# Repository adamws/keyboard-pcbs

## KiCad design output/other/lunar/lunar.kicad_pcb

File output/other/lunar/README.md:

## other/lunar

[layout](lunar-kle.json) - [PCB](lunar.kicad_pcb)

{:loading="lazy"}

[Open in keyboard-layout-editor](http://www.keyboard-layout-editor.com/##@@=0,0&=0,1&=0,2&=0,3&=0,4&=0,5&=0,6&=0,7&=0,8&=0,9&=0,10&=0,11&=0,12&=0,13&=2,12&=0,14;&@_w:1.5;&=1,0&=1,1&=1,2&=1,3&=1,4&=1,5&=1,6&=1,7&=1,8&=1,9&=1,10&=1,11&=1,12&_w:1.5;&=1,13&=1,14;&@_w:1.75;&=2,0&=2,1&=2,2&=2,3&=2,4&=2,5&=2,6&=2,7&=2,8&=2,9&=2,10&=2,11&_w:2.25;&=2,13&=2,14;&@_w:2.25;&=3,0&=3,1&=3,2&=3,3&=3,4&=3,5&=3,6&=3,7&=3,8&=3,9&=3,10&_w:1.75;&=3,11&=3,13&=3,14;&@_w:1.5;&=4,0&_w:1.25;&=4,1&_w:1.5;&=4,2&_w:2.25;&=4,3&_w:1.5;&=4,5&_w:2.75;&=4,7&_w:1.25;&=4,9&=4,10&=4,11&=4,13&=4,14)

{:loading="lazy"}

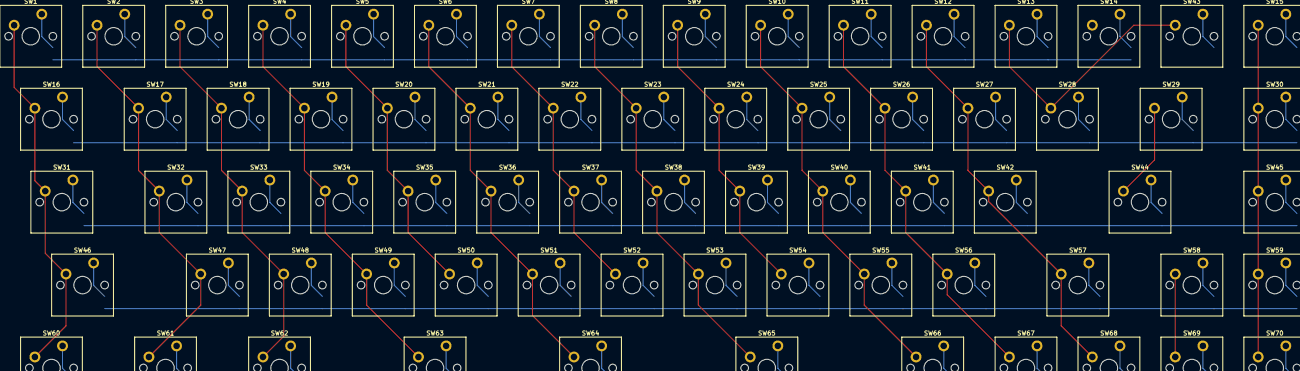
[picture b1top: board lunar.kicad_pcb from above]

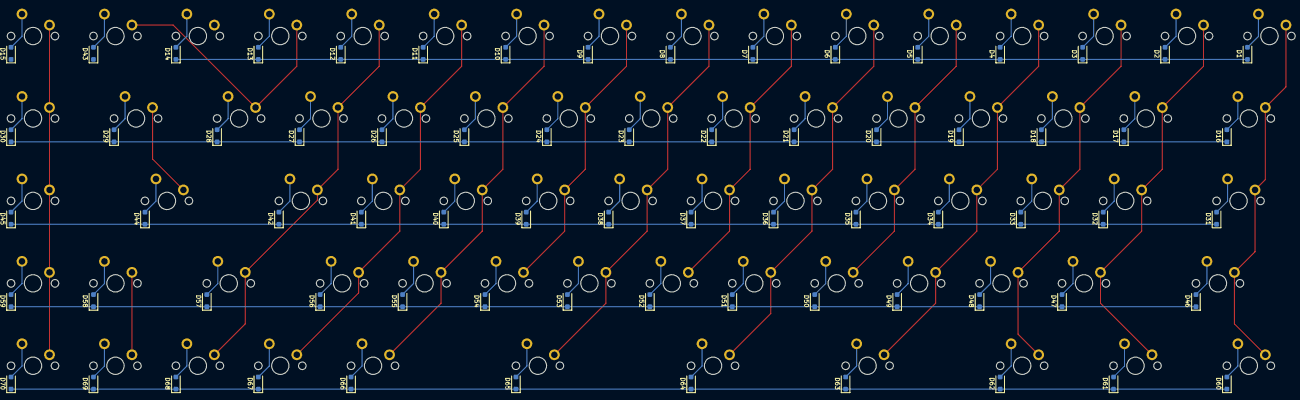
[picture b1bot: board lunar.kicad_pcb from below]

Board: 2 copper layers, 140 parts (70 on the bottom side), 90 nets.

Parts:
D1, D2, D3, D4, D5, D6, D7, D8, D9, D10, D11, D12, D13, D14, D15, D16, D17, D18, D19, D20, D21, D22, D23, D24, D25, D26, D27, D28, D29, D30, D31, D32, D33, D34, D35, D36, D37, D38, D39, D40, D41, D42, D43, D44, D45, D46, D47, D48, D49, D50, D51, D52, D53, D54, D55, D56, D57, D58, D59, D60, D61, D62, D63, D64, D65, D66, D67, D68, D69, D70: D_SOD-123F
SW1, SW2, SW3, SW4, SW5, SW6, SW7, SW8, SW9, SW10, SW11, SW12, SW13, SW14, SW15, SW16, SW17, SW18, SW19, SW20, SW21, SW22, SW23, SW24, SW25, SW26, SW27, SW28, SW29, SW30, SW31, SW32, SW33, SW34, SW35, SW36, SW37, SW38, SW39, SW40, SW41, SW42, SW43, SW44, SW45, SW46, SW47, SW48, SW49, SW50, SW51, SW52, SW53, SW54, SW55, SW56, SW57, SW58, SW59, SW60, SW61, SW62, SW63, SW64, SW65, SW66, SW67, SW68, SW69, SW70: SW_Cherry_MX_PCB_1.00u

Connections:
COL0: SW1.1, SW16.1, SW31.1, SW46.1, SW60.1
COL1: SW2.1, SW17.1, SW32.1, SW47.1, SW61.1
COL2: SW3.1, SW18.1, SW33.1, SW48.1, SW62.1
COL3: SW4.1, SW19.1, SW34.1, SW49.1, SW63.1
COL4: SW5.1, SW20.1, SW35.1, SW50.1
COL5: SW6.1, SW21.1, SW36.1, SW51.1, SW64.1
COL6: SW7.1, SW22.1, SW37.1, SW52.1
COL7: SW8.1, SW23.1, SW38.1, SW53.1, SW65.1
COL8: SW9.1, SW24.1, SW39.1, SW54.1
COL9: SW10.1, SW25.1, SW40.1, SW55.1, SW66.1
COL10: SW11.1, SW26.1, SW41.1, SW56.1, SW67.1
COL11: SW12.1, SW27.1, SW42.1, SW57.1, SW68.1
COL12: SW13.1, SW28.1, SW43.1
COL13: SW14.1, SW29.1, SW44.1, SW58.1, SW69.1
COL14: SW15.1, SW30.1, SW45.1, SW59.1, SW70.1
unnamed: D1.2, SW1.2
unnamed: D2.2, SW2.2
unnamed: D3.2, SW3.2
unnamed: D4.2, SW4.2
unnamed: D5.2, SW5.2
unnamed: D6.2, SW6.2
unnamed: D7.2, SW7.2
unnamed: D8.2, SW8.2
unnamed: D9.2, SW9.2
unnamed: D10.2, SW10.2
unnamed: D11.2, SW11.2
unnamed: D12.2, SW12.2
unnamed: D13.2, SW13.2
unnamed: D14.2, SW14.2
unnamed: D15.2, SW15.2
unnamed: D16.2, SW16.2
unnamed: D17.2, SW17.2
unnamed: D18.2, SW18.2
unnamed: D19.2, SW19.2
unnamed: D20.2, SW20.2
unnamed: D21.2, SW21.2
unnamed: D22.2, SW22.2
unnamed: D23.2, SW23.2
unnamed: D24.2, SW24.2
unnamed: D25.2, SW25.2
unnamed: D26.2, SW26.2
unnamed: D27.2, SW27.2
unnamed: D28.2, SW28.2
unnamed: D29.2, SW29.2
unnamed: D30.2, SW30.2
unnamed: D31.2, SW31.2
unnamed: D32.2, SW32.2
unnamed: D33.2, SW33.2
unnamed: D34.2, SW34.2
unnamed: D35.2, SW35.2
unnamed: D36.2, SW36.2
unnamed: D37.2, SW37.2
unnamed: D38.2, SW38.2
unnamed: D39.2, SW39.2
unnamed: D40.2, SW40.2
unnamed: D41.2, SW41.2
unnamed: D42.2, SW42.2
unnamed: D43.2, SW43.2
unnamed: D44.2, SW44.2
unnamed: D45.2, SW45.2
unnamed: D46.2, SW46.2
unnamed: D47.2, SW47.2
unnamed: D48.2, SW48.2
unnamed: D49.2, SW49.2
unnamed: D50.2, SW50.2
unnamed: D51.2, SW51.2
unnamed: D52.2, SW52.2
unnamed: D53.2, SW53.2
unnamed: D54.2, SW54.2
unnamed: D55.2, SW55.2
unnamed: D56.2, SW56.2
unnamed: D57.2, SW57.2
unnamed: D58.2, SW58.2
unnamed: D59.2, SW59.2
unnamed: D60.2, SW60.2
unnamed: D61.2, SW61.2
unnamed: D62.2, SW62.2
unnamed: D63.2, SW63.2
unnamed: D64.2, SW64.2
unnamed: D65.2, SW65.2
unnamed: D66.2, SW66.2
unnamed: D67.2, SW67.2
unnamed: D68.2, SW68.2
unnamed: D69.2, SW69.2
unnamed: D70.2, SW70.2
ROW0: D1.1, D2.1, D3.1, D4.1, D5.1, D6.1, D7.1, D8.1, D9.1, D10.1, D11.1, D12.1, D13.1, D14.1, D15.1
ROW1: D16.1, D17.1, D18.1, D19.1, D20.1, D21.1, D22.1, D23.1, D24.1, D25.1, D26.1, D27.1, D28.1, D29.1, D30.1
ROW2: D31.1, D32.1, D33.1, D34.1, D35.1, D36.1, D37.1, D38.1, D39.1, D40.1, D41.1, D42.1, D43.1, D44.1, D45.1
ROW3: D46.1, D47.1, D48.1, D49.1, D50.1, D51.1, D52.1, D53.1, D54.1, D55.1, D56.1, D57.1, D58.1, D59.1
ROW4: D60.1, D61.1, D62.1, D63.1, D64.1, D65.1, D66.1, D67.1, D68.1, D69.1, D70.1

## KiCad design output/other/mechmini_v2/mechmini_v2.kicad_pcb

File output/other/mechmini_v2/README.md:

## other/mechmini_v2

[layout](mechmini_v2-kle.json) - [PCB](mechmini_v2.kicad_pcb)

{:loading="lazy"}

[Open in keyboard-layout-editor](http://www.keyboard-layout-editor.com/##@@_c=#aaaaaa;&=0,0&_c=#cccccc;&=0,1&=0,2&=0,3&=0,4&=0,5&=0,6&=0,7&=0,8&=0,9&=0,10&_c=#aaaaaa;&=0,11;&@=1,0%0A%0A%0A0,0&_c=#cccccc;&=1,1%0A%0A%0A0,0&=1,2%0A%0A%0A0,0&=1,3%0A%0A%0A0,0&=1,4%0A%0A%0A0,0&=1,5%0A%0A%0A0,0&=1,6%0A%0A%0A0,0&=1,7%0A%0A%0A0,0&=1,8%0A%0A%0A0,0&=1,9%0A%0A%0A0,0&=1,10%0A%0A%0A0,0&_c=#aaaaaa;&=1,11%0A%0A%0A0,0;&@=2,0%0A%0A%0A0,0&_c=#cccccc;&=2,1%0A%0A%0A0,0&=2,2%0A%0A%0A0,0&=2,3%0A%0A%0A0,0&=2,4%0A%0A%0A0,0&=2,5%0A%0A%0A0,0&=2,6%0A%0A%0A0,0&=2,7%0A%0A%0A0,0&=2,8%0A%0A%0A0,0&=2,9%0A%0A%0A0,0&=2,10%0A%0A%0A0,0&_c=#aaaaaa;&=2,11%0A%0A%0A0,0;&@=3,0%0A%0A%0A0,0&=3,1%0A%0A%0A0,0&=3,2%0A%0A%0A0,0&=3,3%0A%0A%0A0,0&=3,4%0A%0A%0A0,0&=3,5%0A%0A%0A0,0&=3,6%0A%0A%0A0,0&=3,7%0A%0A%0A0,0&=3,8%0A%0A%0A0,0&=3,9%0A%0A%0A0,0&=3,10%0A%0A%0A0,0&=3,11%0A%0A%0A0,0;&@_x:13.25&y:-3;&=1,0%0A%0A%0A0,1&_c=#cccccc;&=1,1%0A%0A%0A0,1&=1,2%0A%0A%0A0,1&=1,3%0A%0A%0A0,1&=1,4%0A%0A%0A0,1&=1,5%0A%0A%0A0,1&=1,6%0A%0A%0A0,1&=1,7%0A%0A%0A0,1&=1,8%0A%0A%0A0,1&=1,9%0A%0A%0A0,1&=1,10%0A%0A%0A0,1&_c=#aaaaaa;&=1,11%0A%0A%0A0,1;&@_x:13.25;&=2,0%0A%0A%0A0,1&_c=#cccccc;&=2,1%0A%0A%0A0,1&=2,2%0A%0A%0A0,1&=2,3%0A%0A%0A0,1&=2,4%0A%0A%0A0,1&=2,5%0A%0A%0A0,1&=2,6%0A%0A%0A0,1&=2,7%0A%0A%0A0,1&=2,8%0A%0A%0A0,1&=2,9%0A%0A%0A0,1&=2,10%0A%0A%0A0,1&_c=#aaaaaa;&=2,11%0A%0A%0A0,1;&@_x:13.25;&=3,0%0A%0A%0A0,1&=3,1%0A%0A%0A0,1&=3,2%0A%0A%0A0,1&=3,3%0A%0A%0A0,1&=3,4%0A%0A%0A0,1&_c=#cccccc&w:2;&=3,5%0A%0A%0A0,1&_c=#aaaaaa;&=3,7%0A%0A%0A0,1&=3,8%0A%0A%0A0,1&=3,9%0A%0A%0A0,1&=3,10%0A%0A%0A0,1&=3,11%0A%0A%0A0,1;&@_y:1&w:1.25;&=1,0%0A%0A%0A0,2&_c=#cccccc;&=1,1%0A%0A%0A0,2&=1,2%0A%0A%0A0,2&=1,3%0A%0A%0A0,2&=1,4%0A%0A%0A0,2&=1,5%0A%0A%0A0,2&=1,6%0A%0A%0A0,2&=1,7%0A%0A%0A0,2&=1,8%0A%0A%0A0,2&=1,9%0A%0A%0A0,2&_c=#777777&w:1.75;&=1,11%0A%0A%0A0,2&_x:1.25&c=#aaaaaa&w:1.25;&=1,0%0A%0A%0A0,3&_c=#cccccc;&=1,1%0A%0A%0A0,3&=1,2%0A%0A%0A0,3&=1,3%0A%0A%0A0,3&=1,4%0A%0A%0A0,3&=1,5%0A%0A%0A0,3&=1,6%0A%0A%0A0,3&=1,7%0A%0A%0A0,3&=1,8%0A%0A%0A0,3&=1,9%0A%0A%0A0,3&_c=#777777&w:1.75;&=1,11%0A%0A%0A0,3;&@_c=#aaaaaa&w:1.75;&=2,0%0A%0A%0A0,2&_c=#cccccc;&=2,2%0A%0A%0A0,2&=2,3%0A%0A%0A0,2&=2,4%0A%0A%0A0,2&=2,5%0A%0A%0A0,2&=2,6%0A%0A%0A0,2&=2,7%0A%0A%0A0,2&=2,8%0A%0A%0A0,2&=2,9%0A%0A%0A0,2&_w:1.25;&=2,10%0A%0A%0A0,2&_c=#aaaaaa;&=2,11%0A%0A%0A0,2&_x:1.25&w:1.75;&=2,0%0A%0A%0A0,3&_c=#cccccc;&=2,2%0A%0A%0A0,3&=2,3%0A%0A%0A0,3&=2,4%0A%0A%0A0,3&=2,5%0A%0A%0A0,3&=2,6%0A%0A%0A0,3&=2,7%0A%0A%0A0,3&=2,8%0A%0A%0A0,3&=2,9%0A%0A%0A0,3&_w:1.25;&=2,10%0A%0A%0A0,3&_c=#aaaaaa;&=2,11%0A%0A%0A0,3;&@_w:1.25;&=3,0%0A%0A%0A0,2&=3,1%0A%0A%0A0,2&_w:1.25;&=3,2%0A%0A%0A0,2&_c=#cccccc&w:2.75;&=3,4%0A%0A%0A0,2&_w:2.25;&=3,7%0A%0A%0A0,2&_c=#aaaaaa&w:1.25;&=3,9%0A%0A%0A0,2&=3,10%0A%0A%0A0,2&_w:1.25;&=3,11%0A%0A%0A0,2&_x:1.25&w:1.25;&=3,0%0A%0A%0A0,3&=3,1%0A%0A%0A0,3&=3,2%0A%0A%0A0,3&_c=#cccccc&w:6.25;&=3,6%0A%0A%0A0,3&_c=#aaaaaa&w:1.25;&=3,10%0A%0A%0A0,3&_w:1.25;&=3,11%0A%0A%0A0,3)

{:loading="lazy"}

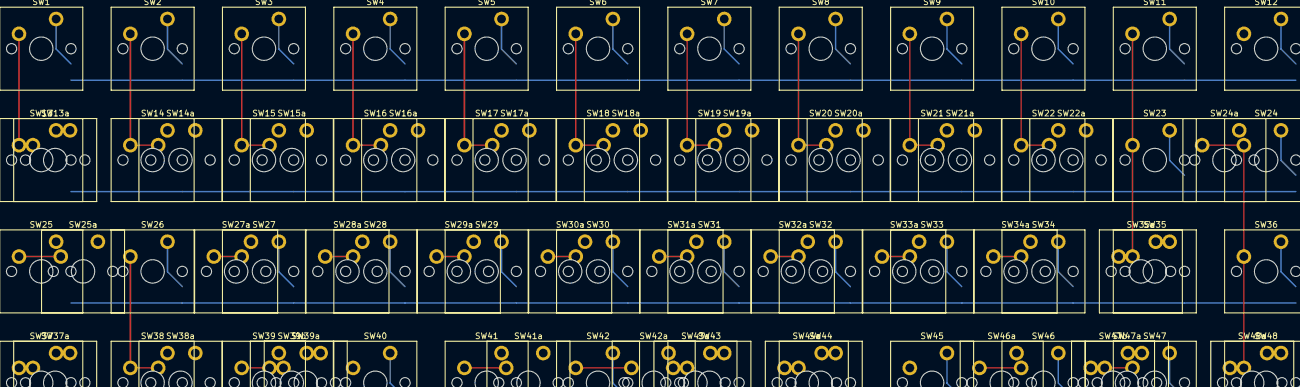
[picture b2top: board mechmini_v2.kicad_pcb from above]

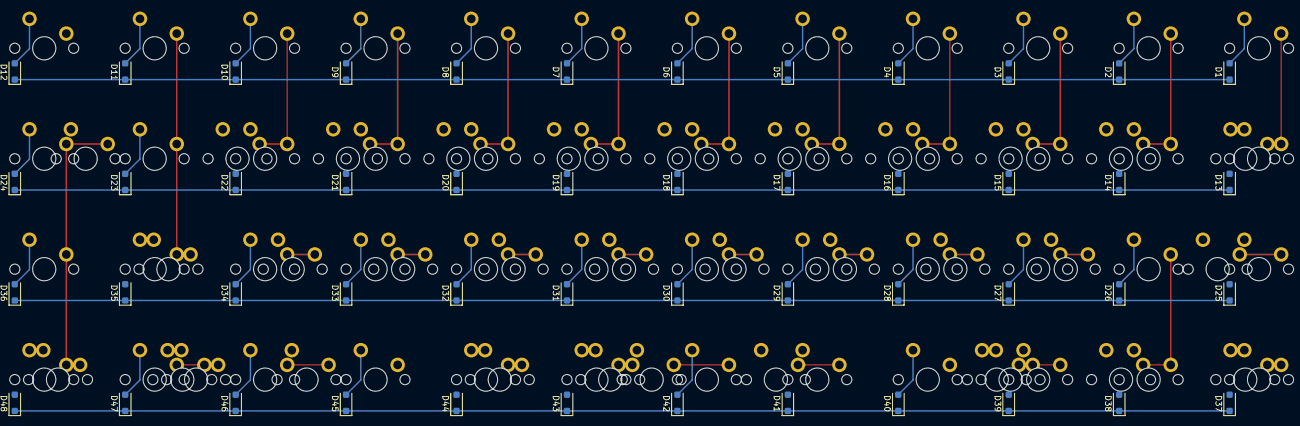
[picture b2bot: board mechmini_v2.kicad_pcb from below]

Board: 2 copper layers, 129 parts (48 on the bottom side), 64 nets.

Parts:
D1, D2, D3, D4, D5, D6, D7, D8, D9, D10, D11, D12, D13, D14, D15, D16, D17, D18, D19, D20, D21, D22, D23, D24, D25, D26, D27, D28, D29, D30, D31, D32, D33, D34, D35, D36, D37, D38, D39, D40, D41, D42, D43, D44, D45, D46, D47, D48: D_SOD-123F
SW1, SW2, SW3, SW4, SW5, SW6, SW7, SW8, SW9, SW10, SW11, SW12, SW13, SW13a, SW14, SW14a, SW15, SW15a, SW16, SW16a, SW17, SW17a, SW18, SW18a, SW19, SW19a, SW20, SW20a, SW21, SW21a, SW22, SW22a, SW23, SW24, SW24a, SW25, SW25a, SW26, SW27, SW27a, SW28, SW28a, SW29, SW29a, SW30, SW30a, SW31, SW31a, SW32, SW32a, SW33, SW33a, SW34, SW34a, SW35, SW35a, SW36, SW37, SW37a, SW38, SW38a, SW39, SW39a, SW39b, SW40, SW41, SW41a, SW42, SW42a, SW43, SW43a, SW44, SW44a, SW45, SW46, SW46a, SW47, SW47a, SW47b, SW48, SW48a: SW_Cherry_MX_PCB_1.00u

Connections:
COL0: SW1.1, SW13.1, SW13a.1, SW25.1, SW25a.1, SW37.1, SW37a.1
COL1: SW2.1, SW14.1, SW14a.1, SW26.1, SW38.1, SW38a.1
COL2: SW3.1, SW15.1, SW15a.1, SW27.1, SW27a.1, SW39.1, SW39a.1, SW39b.1
COL3: SW4.1, SW16.1, SW16a.1, SW28.1, SW28a.1, SW40.1
COL4: SW5.1, SW17.1, SW17a.1, SW29.1, SW29a.1, SW41.1, SW41a.1
COL5: SW6.1, SW18.1, SW18a.1, SW30.1, SW30a.1, SW42.1, SW42a.1
COL6: SW7.1, SW19.1, SW19a.1, SW31.1, SW31a.1, SW43.1, SW43a.1
COL7: SW8.1, SW20.1, SW20a.1, SW32.1, SW32a.1, SW44.1, SW44a.1
COL8: SW9.1, SW21.1, SW21a.1, SW33.1, SW33a.1, SW45.1
COL9: SW10.1, SW22.1, SW22a.1, SW34.1, SW34a.1, SW46.1, SW46a.1
COL10: SW11.1, SW23.1, SW35.1, SW35a.1, SW47.1, SW47a.1, SW47b.1
COL11: SW12.1, SW24.1, SW24a.1, SW36.1, SW48.1, SW48a.1
unnamed: D1.2, SW1.2
unnamed: D2.2, SW2.2
unnamed: D3.2, SW3.2
unnamed: D4.2, SW4.2
unnamed: D5.2, SW5.2
unnamed: D6.2, SW6.2
unnamed: D7.2, SW7.2
unnamed: D8.2, SW8.2
unnamed: D9.2, SW9.2
unnamed: D10.2, SW10.2
unnamed: D11.2, SW11.2
unnamed: D12.2, SW12.2
unnamed: D13.2, SW13.2, SW13a.2
unnamed: D14.2, SW14.2, SW14a.2
unnamed: D15.2, SW15.2, SW15a.2
unnamed: D16.2, SW16.2, SW16a.2
unnamed: D17.2, SW17.2, SW17a.2
unnamed: D18.2, SW18.2, SW18a.2
unnamed: D19.2, SW19.2, SW19a.2
unnamed: D20.2, SW20.2, SW20a.2
unnamed: D21.2, SW21.2, SW21a.2
unnamed: D22.2, SW22.2, SW22a.2
unnamed: D23.2, SW23.2
unnamed: D24.2, SW24.2, SW24a.2
unnamed: D25.2, SW25.2, SW25a.2
unnamed: D26.2, SW26.2
unnamed: D27.2, SW27.2, SW27a.2
unnamed: D28.2, SW28.2, SW28a.2
unnamed: D29.2, SW29.2, SW29a.2
unnamed: D30.2, SW30.2, SW30a.2
unnamed: D31.2, SW31.2, SW31a.2
unnamed: D32.2, SW32.2, SW32a.2
unnamed: D33.2, SW33.2, SW33a.2
unnamed: D34.2, SW34.2, SW34a.2
unnamed: D35.2, SW35.2, SW35a.2
unnamed: D36.2, SW36.2
unnamed: D37.2, SW37.2, SW37a.2
unnamed: D38.2, SW38.2, SW38a.2
unnamed: D39.2, SW39.2, SW39a.2, SW39b.2
unnamed: D40.2, SW40.2
unnamed: D41.2, SW41.2, SW41a.2
unnamed: D42.2, SW42.2, SW42a.2
unnamed: D43.2, SW43.2, SW43a.2
unnamed: D44.2, SW44.2, SW44a.2
unnamed: D45.2, SW45.2
unnamed: D46.2, SW46.2, SW46a.2
unnamed: D47.2, SW47.2, SW47a.2, SW47b.2
unnamed: D48.2, SW48.2, SW48a.2
ROW0: D1.1, D2.1, D3.1, D4.1, D5.1, D6.1, D7.1, D8.1, D9.1, D10.1, D11.1, D12.1
ROW1: D13.1, D14.1, D15.1, D16.1, D17.1, D18.1, D19.1, D20.1, D21.1, D22.1, D23.1, D24.1
ROW2: D25.1, D26.1, D27.1, D28.1, D29.1, D30.1, D31.1, D32.1, D33.1, D34.1, D35.1, D36.1
ROW3: D37.1, D38.1, D39.1, D40.1, D41.1, D42.1, D43.1, D44.1, D45.1, D46.1, D47.1, D48.1
